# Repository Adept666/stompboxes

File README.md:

# -ТТКРЧПДЛ- / Тут короче педали

Здесь хранятся схемы и чертежи гитарных педалек *-ТТКРЧПДЛ-* (штаб-квартира: Омск, Сибирь). Купить педальки и задать вопросы можно через группу [ВКонтакте](https://vk.com/stompboxes), [Telegram-канал](https://t.me/stompboxes) или [Авито](https://www.avito.ru/brands/177f59860cf553edd7d790a341953521). Заценить звук можно на [YouTube-канале](https://youtube.com/channel/UCtStMn9qLL_V5MzlzgSMkUA). Поддержать можно с помощью [Boosty](https://boosty.to/stompboxes). Проект катастрофически убыточен и за семь лет съел тонну моих личных средств.

## Big Muff [REV3]

[Gerber](/PCBS-PCAS/ТКП-3.30.A/output/big_muff_r3a_gerber.zip)

### Bass

[Schematic](/PCBS-PCAS/ТКП-3.30.A/ТКП-1.30.A-2/output/ТКП-1.30.A-2-SCH.pdf)

[F_Fab](/PCBS-PCAS/ТКП-3.30.A/ТКП-1.30.A-2/output/ТКП-1.30.A-2-FAB-TOP.pdf)

[B_Fab](/PCBS-PCAS/ТКП-3.30.A/ТКП-1.30.A-2/output/ТКП-1.30.A-2-FAB-BOTTOM.pdf)

### Bass SM

[Schematic](/PCBS-PCAS/ТКП-3.30.A/ТКП-1.30.A-4/output/ТКП-1.30.A-4-SCH.pdf)

[F_Fab](/PCBS-PCAS/ТКП-3.30.A/ТКП-1.30.A-4/output/ТКП-1.30.A-4-FAB-TOP.pdf)

[B_Fab](/PCBS-PCAS/ТКП-3.30.A/ТКП-1.30.A-4/output/ТКП-1.30.A-4-FAB-BOTTOM.pdf)

### NYC

[Schematic](/PCBS-PCAS/ТКП-3.30.A/ТКП-1.30.A-1/output/ТКП-1.30.A-1-SCH.pdf)

[F_Fab](/PCBS-PCAS/ТКП-3.30.A/ТКП-1.30.A-1/output/ТКП-1.30.A-1-FAB-TOP.pdf)

[B_Fab](/PCBS-PCAS/ТКП-3.30.A/ТКП-1.30.A-1/output/ТКП-1.30.A-1-FAB-BOTTOM.pdf)

### NYC SM

[Schematic](/PCBS-PCAS/ТКП-3.30.A/ТКП-1.30.A-3/output/ТКП-1.30.A-3-SCH.pdf)

[F_Fab](/PCBS-PCAS/ТКП-3.30.A/ТКП-1.30.A-3/output/ТКП-1.30.A-3-FAB-TOP.pdf)

[B_Fab](/PCBS-PCAS/ТКП-3.30.A/ТКП-1.30.A-3/output/ТКП-1.30.A-3-FAB-BOTTOM.pdf)

## Big Muff [REV2]

[Gerber](/PCBS-PCAS/ТКП-3.13.A/output/big_muff_r2a_gerber.zip)

### Bass

[Schematic](/PCBS-PCAS/ТКП-3.13.A/ТКП-1.13.A-2/output/ТКП-1.13.A-2-SCH.pdf)

[F_Fab](/PCBS-PCAS/ТКП-3.13.A/ТКП-1.13.A-2/output/ТКП-1.13.A-2-FAB-TOP.pdf)

[B_Fab](/PCBS-PCAS/ТКП-3.13.A/ТКП-1.13.A-2/output/ТКП-1.13.A-2-FAB-BOTTOM.pdf)

### NYC

[Schematic](/PCBS-PCAS/ТКП-3.13.A/ТКП-1.13.A-1/output/ТКП-1.13.A-1-SCH.pdf)

[F_Fab](/PCBS-PCAS/ТКП-3.13.A/ТКП-1.13.A-1/output/ТКП-1.13.A-1-FAB-TOP.pdf)

[B_Fab](/PCBS-PCAS/ТКП-3.13.A/ТКП-1.13.A-1/output/ТКП-1.13.A-1-FAB-BOTTOM.pdf)

## Crumbwave Multiplexer [REV1]

[Schematic](/PCBS-PCAS/ТКП-3.32.A/ТКП-1.32.A-1/output/ТКП-1.32.A-1-SCH.pdf)

[F_Fab](/PCBS-PCAS/ТКП-3.32.A/ТКП-1.32.A-1/output/ТКП-1.32.A-1-FAB-TOP.pdf)

[B_Fab](/PCBS-PCAS/ТКП-3.32.A/ТКП-1.32.A-1/output/ТКП-1.32.A-1-FAB-BOTTOM.pdf)

[Gerber](/PCBS-PCAS/ТКП-3.32.A/output/crumbwave_multiplexer_r1a_gerber.zip)

## Deep Blue Delay [REV3]

### [REV3C]

[Gerber](/PCBS-PCAS/ТКП-3.17.C/output/deep_blue_delay_r3c_gerber.zip)

### [C]

[Schematic](/PCBS-PCAS/ТКП-3.17.C/ТКП-1.17.C-1/output/ТКП-1.17.C-1-SCH.pdf)

[F_Fab](/PCBS-PCAS/ТКП-3.17.C/ТКП-1.17.C-1/output/ТКП-1.17.C-1-FAB-TOP.pdf)

### [C] SM

[Schematic](/PCBS-PCAS/ТКП-3.17.C/ТКП-1.17.C-2/output/ТКП-1.17.C-2-SCH.pdf)

[F_Fab](/PCBS-PCAS/ТКП-3.17.C/ТКП-1.17.C-2/output/ТКП-1.17.C-2-FAB-TOP.pdf)

### [REV3B]

[Gerber](/PCBS-PCAS/ТКП-3.17.B/output/deep_blue_delay_r3b_gerber.zip)

### [B]

[Schematic](/PCBS-PCAS/ТКП-3.17.B/ТКП-1.17.B-1/output/ТКП-1.17.B-1-SCH.pdf)

[F_Fab](/PCBS-PCAS/ТКП-3.17.B/ТКП-1.17.B-1/output/ТКП-1.17.B-1-FAB-TOP.pdf)

[B_Fab](/PCBS-PCAS/ТКП-3.17.B/ТКП-1.17.B-1/output/ТКП-1.17.B-1-FAB-BOTTOM.pdf)

### [B] SM

[Schematic](/PCBS-PCAS/ТКП-3.17.B/ТКП-1.17.B-2/output/ТКП-1.17.B-2-SCH.pdf)

[F_Fab](/PCBS-PCAS/ТКП-3.17.B/ТКП-1.17.B-2/output/ТКП-1.17.B-2-FAB-TOP.pdf)

[B_Fab](/PCBS-PCAS/ТКП-3.17.B/ТКП-1.17.B-2/output/ТКП-1.17.B-2-FAB-BOTTOM.pdf)

## Distortion + [REV2]

[Schematic](/PCBS-PCAS/ТКП-3.11.A/ТКП-1.11.A-1/output/ТКП-1.11.A-1-SCH.pdf)

[F_Fab](/PCBS-PCAS/ТКП-3.11.A/ТКП-1.11.A-1/output/ТКП-1.11.A-1-FAB-TOP.pdf)

[Gerber](/PCBS-PCAS/ТКП-3.11.A/output/distortion_+_r2a_gerber.zip)

## Edamamer [REV1]

[Schematic](/PCBS-PCAS/ТКП-3.28.A/ТКП-1.28.A-1/output/ТКП-1.28.A-1-SCH.pdf)

[F_Fab](/PCBS-PCAS/ТКП-3.28.A/ТКП-1.28.A-1/output/ТКП-1.28.A-1-FAB-TOP.pdf)

[B_Fab](/PCBS-PCAS/ТКП-3.28.A/ТКП-1.28.A-1/output/ТКП-1.28.A-1-FAB-BOTTOM.pdf)

[Gerber](/PCBS-PCAS/ТКП-3.28.A/output/edamamer_r1a_gerber.zip)

## Fishtaur [REV1]

### [REV1A]

[Gerber](/PCBS-PCAS/ТКП-3.21.A/output/fishtaur_r1a_gerber.zip)

### [A]

[Schematic](/PCBS-PCAS/ТКП-3.21.A/ТКП-1.21.A-1/output/ТКП-1.21.A-1-SCH.pdf)

[F_Fab](/PCBS-PCAS/ТКП-3.21.A/ТКП-1.21.A-1/output/ТКП-1.21.A-1-FAB-TOP.pdf)

### [A] SM

[Schematic](/PCBS-PCAS/ТКП-3.21.A/ТКП-1.21.A-2/output/ТКП-1.21.A-2-SCH.pdf)

[F_Fab](/PCBS-PCAS/ТКП-3.21.A/ТКП-1.21.A-2/output/ТКП-1.21.A-2-FAB-TOP.pdf)

## Fuzz Factory [REV1]

### Main Board [REV1D] / Potentiometer Board [REV1C]

[Schematic](/PCBS-PCAS/ТКП-3.14.D-ТКП-3.15.C/ТКП-1.14.D-1-ТКП-1.15.C-1/output/ТКП-1.14.D-1-ТКП-1.15.C-1-SCH.pdf)

[F_Fab](/PCBS-PCAS/ТКП-3.14.D-ТКП-3.15.C/ТКП-1.14.D-1-ТКП-1.15.C-1/output/ТКП-1.14.D-1-ТКП-1.15.C-1-FAB-TOP.pdf)

[Gerber (Main Board)](/PCBS-PCAS/ТКП-3.14.D-ТКП-3.15.C/output/fuzz_factory_main_board_r1d_gerber.zip)

[Gerber (Potentiometer Board)](/PCBS-PCAS/ТКП-3.14.D-ТКП-3.15.C/output/fuzz_factory_potentiometer_board_r1c_gerber.zip)

### Main Board [REV1C] / Potentiometer Board [REV1B]

[Schematic](/PCBS-PCAS/ТКП-3.14.C-ТКП-3.15.B/ТКП-1.14.C-1-ТКП-1.15.B-1/output/ТКП-1.14.C-1-ТКП-1.15.B-1-SCH.pdf)

[F_Fab](/PCBS-PCAS/ТКП-3.14.C-ТКП-3.15.B/ТКП-1.14.C-1-ТКП-1.15.B-1/output/ТКП-1.14.C-1-ТКП-1.15.B-1-FAB-TOP.pdf)

[Gerber (Main Board)](/PCBS-PCAS/ТКП-3.14.C-ТКП-3.15.B/output/fuzz_factory_main_board_r1c_gerber.zip)

[Gerber (Potentiometer Board)](/PCBS-PCAS/ТКП-3.14.B-ТКП-3.15.B/output/fuzz_factory_potentiometer_board_r1b_gerber.zip)

### Main Board [REV1B] / Potentiometer Board [REV1B]

[Schematic](/PCBS-PCAS/ТКП-3.14.B-ТКП-3.15.B/ТКП-1.14.B-1-ТКП-1.15.B-1/output/ТКП-1.14.B-1-ТКП-1.15.B-1-SCH.pdf)

[F_Fab](/PCBS-PCAS/ТКП-3.14.B-ТКП-3.15.B/ТКП-1.14.B-1-ТКП-1.15.B-1/output/ТКП-1.14.B-1-ТКП-1.15.B-1-FAB-TOP.pdf)

[B_Cuts](/PCBS-PCAS/ТКП-3.14.B-ТКП-3.15.B/ТКП-1.14.B-1-ТКП-1.15.B-1/output/ТКП-1.14.B-1-ТКП-1.15.B-1-CUTS-BOTTOM.pdf)

[B_Jumpers](/PCBS-PCAS/ТКП-3.14.B-ТКП-3.15.B/ТКП-1.14.B-1-ТКП-1.15.B-1/output/ТКП-1.14.B-1-ТКП-1.15.B-1-JUMPERS-BOTTOM.pdf)

[Gerber (Main Board)](/PCBS-PCAS/ТКП-3.14.B-ТКП-3.15.B/output/fuzz_factory_main_board_r1b_gerber.zip)

[Gerber (Potentiometer Board)](/PCBS-PCAS/ТКП-3.14.B-ТКП-3.15.B/output/fuzz_factory_potentiometer_board_r1b_gerber.zip)

## Good Grief Overdrive [REV1]

### [REV1B]

[Gerber](/PCBS-PCAS/ТКП-3.19.B/output/good_grief_overdrive_r1b_gerber.zip)

### [B]

[Schematic](/PCBS-PCAS/ТКП-3.19.B/ТКП-1.19.B-1/output/ТКП-1.19.B-1-SCH.pdf)

[F_Fab](/PCBS-PCAS/ТКП-3.19.B/ТКП-1.19.B-1/output/ТКП-1.19.B-1-FAB-TOP.pdf)

### [B] SM

[Schematic](/PCBS-PCAS/ТКП-3.19.B/ТКП-1.19.B-2/output/ТКП-1.19.B-2-SCH.pdf)

[F_Fab](/PCBS-PCAS/ТКП-3.19.B/ТКП-1.19.B-2/output/ТКП-1.19.B-2-FAB-TOP.pdf)

### [REV1A]

[Schematic](/PCBS-PCAS/ТКП-3.19.A/ТКП-1.19.A-1/output/ТКП-1.19.A-1-SCH.pdf)

[F_Fab](/PCBS-PCAS/ТКП-3.19.A/ТКП-1.19.A-1/output/ТКП-1.19.A-1-FAB-TOP.pdf)

[Gerber](/PCBS-PCAS/ТКП-3.19.A/output/good_grief_overdrive_r1a_gerber.zip)

## Great Depression Phaser [REV1]

[Schematic](/PCBS-PCAS/ТКП-3.40.A/ТКП-1.38.A-1/output/ТКП-1.38.A-1-SCH.pdf)

[F_Fab](/PCBS-PCAS/ТКП-3.40.A/ТКП-1.38.A-1/output/ТКП-1.38.A-1-FAB-TOP.pdf)

[B_Fab](/PCBS-PCAS/ТКП-3.40.A/ТКП-1.38.A-1/output/ТКП-1.38.A-1-FAB-BOTTOM.pdf)

[Gerber](/PCBS-PCAS/ТКП-3.40.A/output/phaser_a_r1a_gerber.zip)

## Little Angel Chorus [REV1]

[Schematic](/PCBS-PCAS/ТКП-3.12.A/ТКП-1.12.A-1/output/ТКП-1.12.A-1-SCH.pdf)

[F_Fab](/PCBS-PCAS/ТКП-3.12.A/ТКП-1.12.A-1/output/ТКП-1.12.A-1-FAB-TOP.pdf)

[B_Fab](/PCBS-PCAS/ТКП-3.12.A/ТКП-1.12.A-1/output/ТКП-1.12.A-1-FAB-BOTTOM.pdf)

[Gerber](/PCBS-PCAS/ТКП-3.12.A/output/little_angel_chorus_r1a_gerber.zip)

## Salty Phaser [REV1]

[Schematic](/PCBS-PCAS/ТКП-3.23.A/ТКП-1.23.A-1/output/ТКП-1.23.A-1-SCH.pdf)

[F_Fab](/PCBS-PCAS/ТКП-3.23.A/ТКП-1.23.A-1/output/ТКП-1.23.A-1-FAB-TOP.pdf)

[B_Fab](/PCBS-PCAS/ТКП-3.23.A/ТКП-1.23.A-1/output/ТКП-1.23.A-1-FAB-BOTTOM.pdf)

[F_Cuts](/PCBS-PCAS/ТКП-3.23.A/ТКП-1.23.A-1/output/ТКП-1.23.A-1-CUTS-TOP.pdf)

[B_Cuts](/PCBS-PCAS/ТКП-3.23.A/ТКП-1.23.A-1/output/ТКП-1.23.A-1-CUTS-BOTTOM.pdf)

[F_Jumpers](/PCBS-PCAS/ТКП-3.23.A/ТКП-1.23.A-1/output/ТКП-1.23.A-1-JUMPERS-TOP.pdf)

[B_Jumpers](/PCBS-PCAS/ТКП-3.23.A/ТКП-1.23.A-1/output/ТКП-1.23.A-1-JUMPERS-BOTTOM.pdf)

[Gerber](/PCBS-PCAS/ТКП-3.23.A/output/salty_phaser_r1a_gerber.zip)

## Копка Земли [REV1]

### [REV1B]

[Gerber](/PCBS-PCAS/ТКП-3.24.B/output/копка_земли_r1b_gerber.zip)

### [B] Down-Tuned

[Schematic](/PCBS-PCAS/ТКП-3.24.B/ТКП-1.24.B-1/output/ТКП-1.24.B-1-SCH.pdf)

[F_Fab](/PCBS-PCAS/ТКП-3.24.B/ТКП-1.24.B-1/output/ТКП-1.24.B-1-FAB-TOP.pdf)

### [B] Down-Tuned SM

[Schematic](/PCBS-PCAS/ТКП-3.24.B/ТКП-1.24.B-3/output/ТКП-1.24.B-3-SCH.pdf)

[F_Fab](/PCBS-PCAS/ТКП-3.24.B/ТКП-1.24.B-3/output/ТКП-1.24.B-3-FAB-TOP.pdf)

### [B] Standard-Tuned

[Schematic](/PCBS-PCAS/ТКП-3.24.B/ТКП-1.24.B-2/output/ТКП-1.24.B-2-SCH.pdf)

[F_Fab](/PCBS-PCAS/ТКП-3.24.B/ТКП-1.24.B-2/output/ТКП-1.24.B-2-FAB-TOP.pdf)

### [B] Standard-Tuned SM

[Schematic](/PCBS-PCAS/ТКП-3.24.B/ТКП-1.24.B-4/output/ТКП-1.24.B-4-SCH.pdf)

[F_Fab](/PCBS-PCAS/ТКП-3.24.B/ТКП-1.24.B-4/output/ТКП-1.24.B-4-FAB-TOP.pdf)

### [REV1A]

[Gerber](/PCBS-PCAS/ТКП-3.24.A/output/копка_земли_r1a_gerber.zip)

### [A] Down-Tuned

[Schematic](/PCBS-PCAS/ТКП-3.24.A/ТКП-1.24.A-1/output/ТКП-1.24.A-1-SCH.pdf)

[F_Fab](/PCBS-PCAS/ТКП-3.24.A/ТКП-1.24.A-1/output/ТКП-1.24.A-1-FAB-TOP.pdf)

### [A] Standard-Tuned

[Schematic](/PCBS-PCAS/ТКП-3.24.A/ТКП-1.24.A-2/output/ТКП-1.24.A-2-SCH.pdf)

[F_Fab](/PCBS-PCAS/ТКП-3.24.A/ТКП-1.24.A-2/output/ТКП-1.24.A-2-FAB-TOP.pdf)

## Крыса [REV1]

[Schematic](/PCBS-PCAS/ТКП-3.44.A/ТКП-1.40.A-1/output/ТКП-1.40.A-1-SCH.pdf)

[F_Fab](/PCBS-PCAS/ТКП-3.44.A/ТКП-1.40.A-1/output/ТКП-1.40.A-1-FAB-TOP.pdf)

[Gerber](/PCBS-PCAS/ТКП-3.44.A/output/clipper_a_r1a_gerber.zip)

## Тремоло Саши Огородникова [REV1]

### [REV1B]

[Schematic](/PCBS-PCAS/ТКП-3.25.B/ТКП-1.25.B-1/output/ТКП-1.25.B-1-SCH.pdf)

[F_Fab](/PCBS-PCAS/ТКП-3.25.B/ТКП-1.25.B-1/output/ТКП-1.25.B-1-FAB-TOP.pdf)

[B_Fab](/PCBS-PCAS/ТКП-3.25.B/ТКП-1.25.B-1/output/ТКП-1.25.B-1-FAB-BOTTOM.pdf)

[Gerber](/PCBS-PCAS/ТКП-3.25.B/output/тремоло_саши_огородникова_r1b_gerber.zip)

### [REV1A]

[Schematic](/PCBS-PCAS/ТКП-3.25.A/ТКП-1.25.A-1/output/ТКП-1.25.A-1-SCH.pdf)

[F_Fab](/PCBS-PCAS/ТКП-3.25.A/ТКП-1.25.A-1/output/ТКП-1.25.A-1-FAB-TOP.pdf)

[B_Fab](/PCBS-PCAS/ТКП-3.25.A/ТКП-1.25.A-1/output/ТКП-1.25.A-1-FAB-BOTTOM.pdf)

[F_Cuts](/PCBS-PCAS/ТКП-3.25.A/ТКП-1.25.A-1/output/ТКП-1.25.A-1-CUTS-TOP.pdf)

[B_Cuts](/PCBS-PCAS/ТКП-3.25.A/ТКП-1.25.A-1/output/ТКП-1.25.A-1-CUTS-BOTTOM.pdf)

[B_Jumpers](/PCBS-PCAS/ТКП-3.25.A/ТКП-1.25.A-1/output/ТКП-1.25.A-1-JUMPERS-BOTTOM.pdf)

[Gerber](/PCBS-PCAS/ТКП-3.25.A/output/тремоло_саши_огородникова_r1a_gerber.zip)

## Требования

Работа с исходными файлами осуществляется в программе [KiCad](https://kicad.org).

Для просмотра и редактирования принципиальных схем необходимо подключить следующие библиотеки символов:
* [KCL](https://github.com/Adept666/KCL)
* [SBKCL](/SBKCL)

Для работы с чертежами печатных узлов подключение библиотек не требуется, так как все использованные футпринты вшиты в файлы *.kicad_pcb. При необходимости футпринты могут быть найдены в библиотеках [KCL](https://github.com/Adept666/KCL) и [SBKCL](/SBKCL).

## Авторы

Основной разработчик: *Igor Ivanov* (*Игорь Иванов*).  
Связь: adept.666.1993@gmail.com • [Telegram](https://t.me/adept666_2) • [ВКонтакте](https://vk.com/igor_ivanov_93) • [Google Scholar](https://scholar.google.com/citations?user=dhN1LfkAAAAJ).

Репозиторий также содержит сторонние открытые изображения и шрифты, использованные при создании макетов рисунков, наносимых на корпуса педалей. Информация об авторах и лицензиях представлена в сопроводительных текстовых файлах, размещённых в соответствующих директориях.

## Лицензии

Настоящий репозиторий использует раздельное лицензирование:

* Основная часть файлов распространяется на условиях *GNU General Public License v3.0 or later*, если не указано иное.

* Проекты печатных плат [Clipper A](/PCBS-PCAS/ТКП-3.44.A) и [OCD](/PCBS-PCAS/ТКП-3.45.A) распространяются на условиях *CERN Open Hardware Licence Version 2 - Strongly Reciprocal*.

* Сторонние [изображения](/graphics/source_images) и [шрифты](/graphics/source_fonts) распространяются на условиях иных лицензий, указанных в соответствующих файлах.

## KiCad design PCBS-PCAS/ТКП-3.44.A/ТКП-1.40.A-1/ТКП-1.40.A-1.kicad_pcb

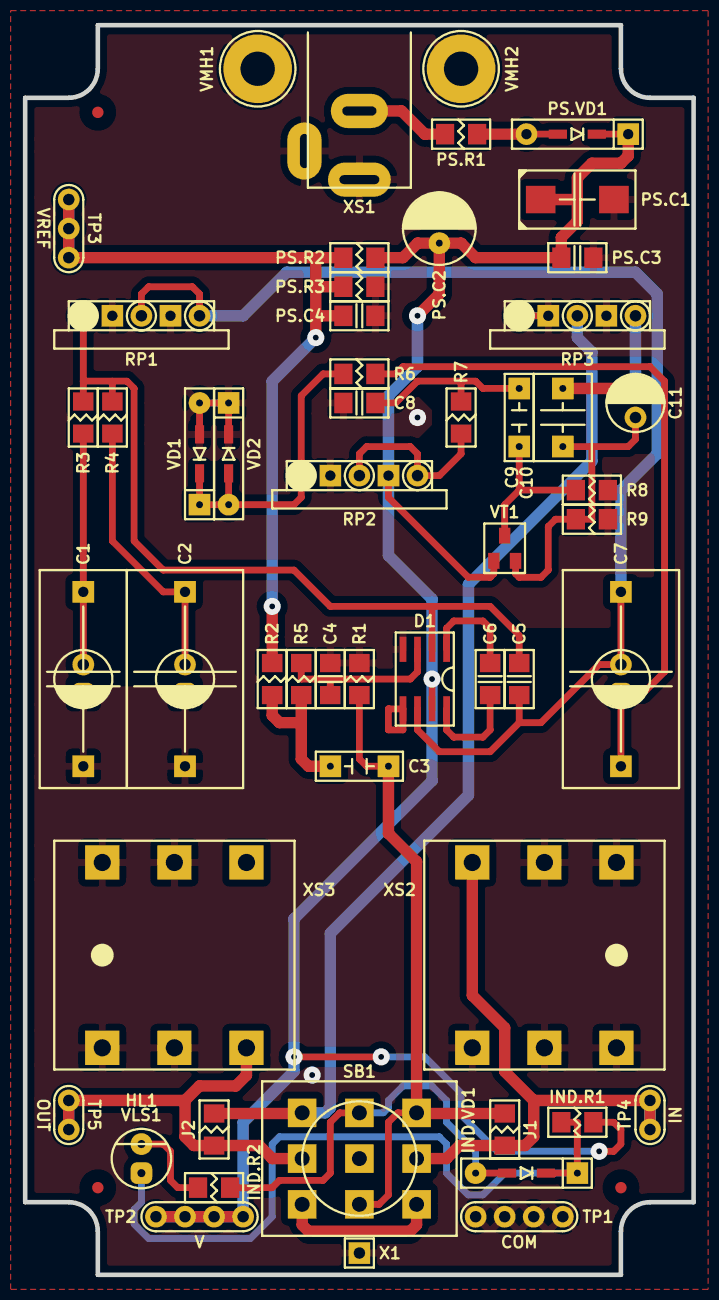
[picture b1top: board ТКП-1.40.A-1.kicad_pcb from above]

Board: 2 copper layers, 58.4 x 109.2 mm, 57 parts (0 on the bottom side), 28 nets.

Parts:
C1: 225; C-RECT-L18.0-W07.0-P15.24-d0.8-OR-CP-RADIAL-D05.0-P02.0-CLS
C2, C7: 475; C-RECT-L18.0-W09.0-P15.24-d0.8-OR-CP-RADIAL-D05.0-P02.0-CLS
C3, C9: 223; C-RECT-L07.3-W02.5-P05.08-d0.5
C4: 102; C-SM-1206
C5: 101; C-SM-1206
C6: X; C-SM-1206
C8: 332; C-SM-1206
C10: X; C-RECT-L07.3-W04.5-P05.08-d0.5
C11: 105; CP-RADIAL-D05.0-P02.0-CLS
D1: 07; P-SO-08
HL1: FYL-5013UWC; LED-ROUND-05.0-UNI-SH-SPACER
IND.R1: 182; R-SM-1206
IND.R2: 682; R-SM-1206
IND.VD1: 5235; P-SOD-123-OR-DO-35-V2
J1, J2: X; R-SM-1206
PS.C1: X; CP-CTSMD-D
PS.C2: 107; CP-RADIAL-D06.3-P02.5-d0.5-CLS
PS.C3: 104; C-SM-1206
PS.C4: 105; C-SM-1206
PS.R1: 470; R-SM-1206
PS.R2, PS.R3: 104; R-SM-1206
PS.VD1: 0540; P-SOD-123-OR-DO-41
R1, R2, R8: 105; R-SM-1206
R3: 470; R-SM-1206
R4: 561; R-SM-1206
R5, R6: 102; R-SM-1206
R7: 152; R-SM-1206
R9: 103; R-SM-1206
RP1, RP2, RP3: A100K; RPB-18-1x17-1.6
SB1: PBS-24-302SP; SW-PBS-24-302SP-2.5
TP1: COM; TP-4-1.0-1.9
TP2: V; TP-4-1.0-1.9
TP3: VREF; TP-3-1.0-1.9
TP4: IN; TP-2-1.0-1.9
TP5: OUT; TP-2-1.0-1.9
VD1, VD2: 4148; P-SOD-123-OR-DO-35-V2
VFM1, VFM2, VFM3: 1.0; VFM-1.0-3.0-SL
VLS1: BR-12.7; VLS-BR-P
VMH1, VMH2: X; VMH-STA-DA5
VT1: 5457; P-SOT-23-D-S-G
X1: X; CON-PAD-S-1.0-1.9
XS1: DC-005; CON-DC-005-9V-OVAL
XS2, XS3: PJ-644C; CON-PJ-644C-IN-OR-OUT

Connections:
/CIR-IN: C3.1, J1.2, R1.2, SB1.NC2, SB1.NO3
/CIR-OUT: J2.1, RP3.2, SB1.NO1
/IN: J1.1, SB1.COM3, TP4.1, XS2.T
/LED: IND.R2.1, IND.VD1.A, SB1.NO2
/OUT: J2.2, SB1.COM1, TP5.1, XS3.T
COM: C1.-, C2.-, C4.2, C8.2, D1.4, PS.C1.-, PS.C2.-, PS.C3.2, PS.C4.2, PS.R3.1, R1.1, R8.1, R9.1, RP1.NC1, RP1.NC2, RP2.NC1, RP3.1, RP3.NC1, RP3.NC2, SB1.COM2, TP1.1, VD1.A, VD2.C, VMH1.0, VMH2.0, X1.1, XS1.C, XS1.SN, XS2.R, XS2.RN, XS2.S, XS2.SN, XS2.TN, XS3.R, XS3.RN, XS3.S, XS3.SN
unnamed: C1.+, R3.1
unnamed: C2.+, R4.1
unnamed: C3.2, R2.2, R5.1
unnamed: C4.1, D1.3, R5.2
unnamed: C5.1, D1.2, R3.2, R4.2, RP1.1
unnamed: C5.2, C7.+, D1.6, RP1.2, RP1.3
unnamed: C6.1, D1.1
unnamed: C6.2, D1.8
unnamed: C7.-, R6.1
unnamed: C8.1, C9.1, R7.2
unnamed: C9.2, R8.2, VT1.G
unnamed: C10.1, C11.+, R9.2, VT1.S
unnamed: C10.2, C11.-, RP3.3
unnamed: HL1.A, IND.R1.2, IND.VD1.C
unnamed: HL1.C, IND.R2.2
unnamed: PS.R1.1, XS1.S
unnamed: PS.R1.2, PS.VD1.A
unnamed: R6.2, RP2.1, VD1.C, VD2.A
unnamed: R7.1, RP2.2, RP2.3
unnamed: SB1.NC1, SB1.NC3
V: D1.7, IND.R1.1, PS.C1.+, PS.C2.+, PS.C3.1, PS.R2.2, PS.VD1.C, RP2.NC2, TP2.1, VT1.D
VREF: PS.C4.1, PS.R2.1, PS.R3.2, R2.1, TP3.1

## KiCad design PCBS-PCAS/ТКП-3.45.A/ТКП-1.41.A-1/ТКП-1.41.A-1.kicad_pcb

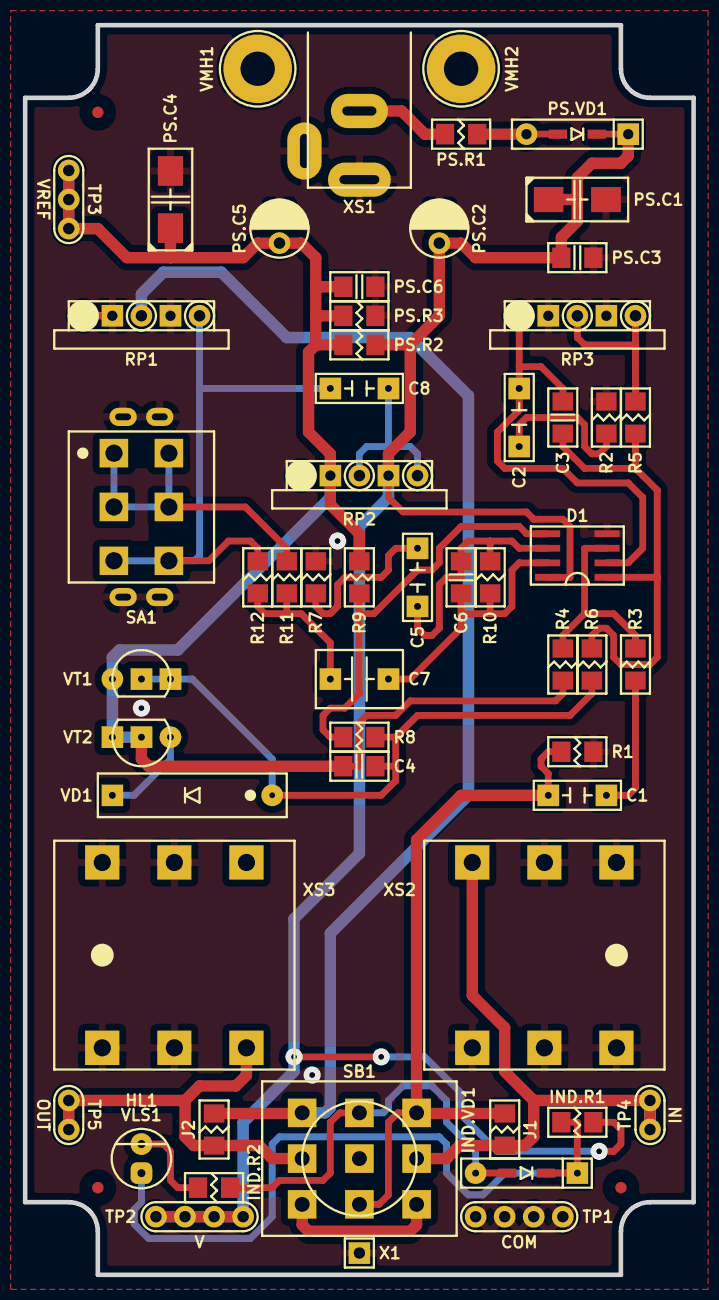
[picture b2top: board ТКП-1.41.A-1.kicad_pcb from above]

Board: 2 copper layers, 58.4 x 109.2 mm, 60 parts (0 on the bottom side), 29 nets.

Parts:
C1: 223; C-RECT-L07.3-W02.5-P05.08-d0.5
C2, C5, C8: 104; C-RECT-L07.3-W02.5-P05.08-d0.5
C3, C6: 221; C-SM-1206
C4: 102; C-SM-1206
C7: 105; C-RECT-L07.3-W04.5-P05.08-d0.5
D1: 082; P-SO-08
HL1: FYL-5013UWC; LED-ROUND-05.0-UNI-SH-SPACER
IND.R1: 182; R-SM-1206
IND.R2: 682; R-SM-1206
IND.VD1: 5235; P-SOD-123-OR-DO-35-V2
J1, J2: X; R-SM-1206
PS.C1: 106 35V; CP-CTSMD-C
PS.C2: 106 35V; CP-RADIAL-D05.0-P02.0-CLS
PS.C3, PS.C6: 104; C-SM-1206
PS.C4: 106 20V; CP-CTSMD-C
PS.C5: 106 25V; CP-RADIAL-D05.0-P02.0-CLS
PS.R1: 330; R-SM-1206
PS.R2, PS.R3: 103; R-SM-1206
PS.VD1: 0540; P-SOD-123-OR-DO-41
R1: 105; R-SM-1206
R2: 222; R-SM-1206
R3, R6, R8: 103; R-SM-1206
R4: 474; R-SM-1206
R5: 183; R-SM-1206
R7: 393; R-SM-1206
R9: 224; R-SM-1206
R10: 154; R-SM-1206
R11: 223; R-SM-1206
R12: 333; R-SM-1206
RP1: B100K; RPB-18-1x17-1.6
RP2: A25K; RPB-18-1x17-1.6
RP3: A500K; RPB-18-1x17-1.6
SA1: MTS-202-A2T; SW-MTS-202-A2T-2.5
SB1: PBS-24-302SP; SW-PBS-24-302SP-2.5
TP1: COM; TP-4-1.0-1.9
TP2: V; TP-4-1.0-1.9
TP3: VREF; TP-3-1.0-1.9
TP4: IN; TP-2-1.0-1.9
TP5: OUT; TP-2-1.0-1.9
VD1: Д9Б; P-Д-9
VFM1, VFM2, VFM3: 1.0; VFM-1.0-3.0-SL
VLS1: BR-12.7; VLS-BR-P
VMH1, VMH2: X; VMH-STA-DA5
VT1, VT2: 7000; P-TO-92-S-G-D
X1: COM; CON-PAD-S-1.0-1.9
XS1: DC-005; CON-DC-005-9V-OVAL
XS2, XS3: PJ-644C; CON-PJ-644C-IN-OR-OUT

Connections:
/CIR-IN: C1.1, J1.2, R1.2, SB1.NC2, SB1.NO3
/CIR-OUT: J2.1, RP1.2, SB1.NO1
/IN: J1.1, SB1.COM3, TP4.1, XS2.T
/LED: IND.R2.1, IND.VD1.A, SB1.NO2
/OUT: J2.2, SB1.COM1, TP5.1, XS3.T
COM: D1.4, PS.C1.-, PS.C2.-, PS.C3.2, PS.C4.-, PS.C5.-, PS.C6.2, PS.R3.1, R1.1, R2.1, R7.1, RP1.1, RP1.NC1, RP1.NC2, RP2.1, RP3.NC1, RP3.NC2, SA1.0, SB1.COM2, TP1.1, VMH1.0, VMH2.0, X1.1, XS1.C, XS1.SN, XS2.R, XS2.RN, XS2.S, XS2.SN, XS2.TN, XS3.R, XS3.RN, XS3.S, XS3.SN
unnamed: C1.2, R3.1
unnamed: C2.1, R2.2
unnamed: C2.2, C3.1, D1.2, RP3.1
unnamed: C3.2, D1.1, R5.1, R6.1
unnamed: C4.1, R6.2, R8.1, VD1.A, VT1.D, VT1.G
unnamed: C5.1, R7.2
unnamed: C5.2, C6.1, D1.6, R10.1
unnamed: C6.2, C7.1, D1.7, R10.2
unnamed: C7.2, R11.1, R12.1
unnamed: C8.1, R12.2, RP1.3, SA1.NO1, SA1.NO2
unnamed: C8.2, RP2.2, RP2.3
unnamed: D1.3, R3.2, R4.2
unnamed: D1.5, R8.2, R9.2
unnamed: HL1.A, IND.R1.2, IND.VD1.C
unnamed: HL1.C, IND.R2.2
unnamed: PS.R1.1, XS1.S
unnamed: PS.R1.2, PS.VD1.A
unnamed: R5.2, RP3.2, RP3.3
unnamed: R11.2, SA1.COM1, SA1.COM2, SA1.NC1, SA1.NC2
unnamed: SB1.NC1, SB1.NC3
unnamed: VD1.C, VT2.S
V: D1.8, IND.R1.1, PS.C1.+, PS.C2.+, PS.C3.1, PS.R2.2, PS.VD1.C, RP2.NC2, TP2.1
VREF: C4.2, PS.C4.+, PS.C5.+, PS.C6.1, PS.R2.1, PS.R3.2, R4.1, R9.1, RP2.NC1, TP3.1, VT1.S, VT2.D, VT2.G

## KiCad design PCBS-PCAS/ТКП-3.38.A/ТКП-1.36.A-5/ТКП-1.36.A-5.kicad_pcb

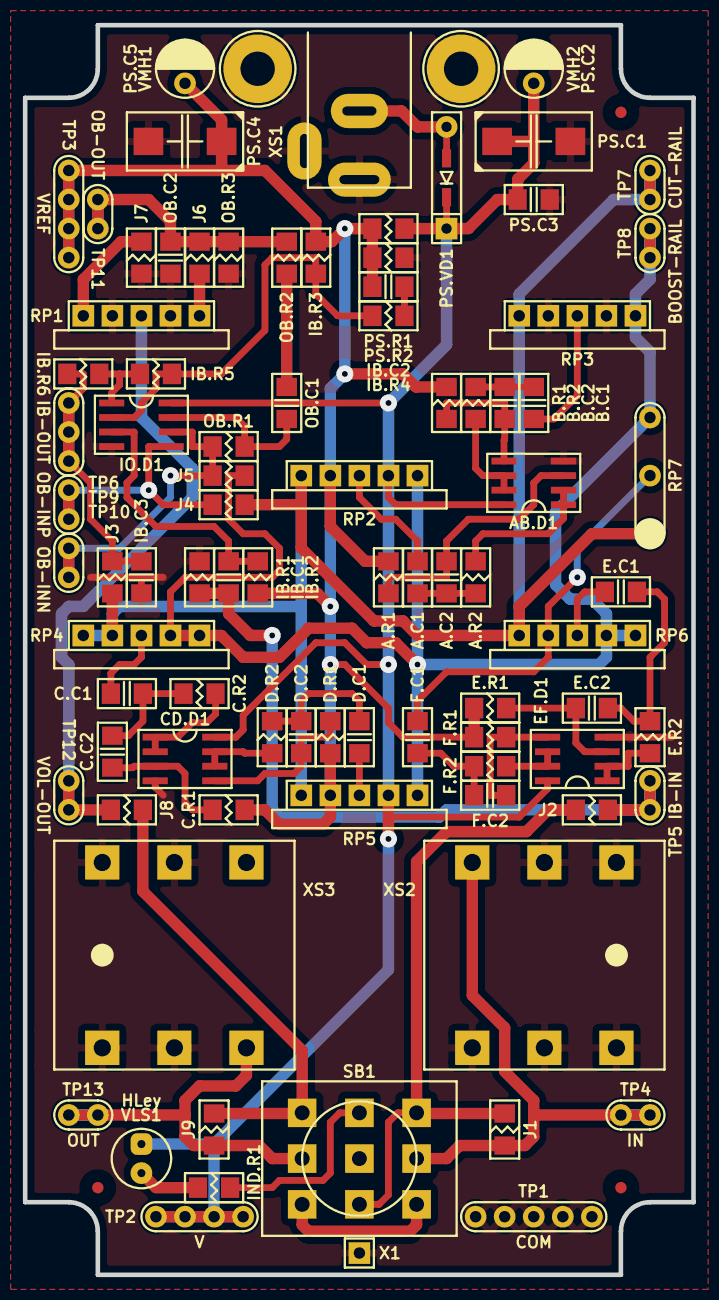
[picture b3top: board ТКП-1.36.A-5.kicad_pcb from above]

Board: 2 copper layers, 58.4 x 109.2 mm, 94 parts (0 on the bottom side), 51 nets.

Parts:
A.C1: 225; C-SM-1206
A.C2: 473; C-SM-1206
A.R1: 124; R-SM-1206
A.R2: 471; R-SM-1206
AB.D1: 4558; P-SO-08
B.C1: 105; C-SM-1206
B.C2: 333; C-SM-1206
B.R1: 104; R-SM-1206
B.R2: 471; R-SM-1206
C.C1: 154; C-SM-1206
C.C2: 682; C-SM-1206
C.R1: 104; R-SM-1206
C.R2: 102; R-SM-1206
CD.D1: 4558; P-SO-08
D.C1: 683; C-SM-1206
D.C2: 332; C-SM-1206
D.R1: 104; R-SM-1206
D.R2: 102; R-SM-1206
E.C1: 223; C-SM-1206
E.C2: 681; C-SM-1206
E.R1: 104; R-SM-1206
E.R2: 102; R-SM-1206
EF.D1: 4558; P-SO-08
F.C1, F.C2: X; C-SM-1206
F.R1, F.R2: X; R-SM-1206
HLeу: FYL-3014UWC; LED-ROUND-05.0-UNI-SH-SPACER-PNL-5.3
IB.C1, IB.C2: 103; C-SM-1206
IB.C3: 151; C-SM-1206
IB.R1: 225; R-SM-1206
IB.R2: 474; R-SM-1206
IB.R3, IB.R5, IB.R6: 103; R-SM-1206
IB.R4: 102; R-SM-1206
IND.R1: 433; R-SM-1206
IO.D1: 4558; P-SO-08
J1, J9: X; R-SM-1206
J2, J3, J4, J5, J6, J7, J8: 0; R-SM-1206
OB.C1: 105; C-SM-1206
OB.C2: 103; C-SM-1206
OB.R1, OB.R2, OB.R3: 103; R-SM-1206
PS.C1: 107; CP-CTSMD-D
PS.C2: 107; CP-RADIAL-D05.0-P02.0-CLS
PS.C3: 104; C-SM-1206
PS.C4: 476; CP-CTSMD-D
PS.C5: 476; CP-RADIAL-D05.0-P02.0-CLS
PS.R1, PS.R2: 473; R-SM-1206
PS.VD1: 0520; P-SOD-123-OR-DO-41
RP1, RP2, RP3, RP4, RP5, RP6: B50K; RPB-18-1x17-1.6-PNL-7.2
RP7: X; RP-EXTERNAL
SB1: PBS-24-302SP; SW-PBS-24-302SP-2.5-PNL-12.0
TP1: COM; TP-5-1.0-1.9
TP2: V; TP-4-1.0-1.9
TP3: VREF; TP-4-1.0-1.9
TP4: IN; TP-2-1.0-1.9
TP5: IB-IN; TP-2-1.0-1.9
TP6: IB-OUT; TP-3-1.0-1.9
TP7: CUT-RAIL; TP-2-1.0-1.9
TP8: BOOST-RAIL; TP-2-1.0-1.9
TP9: OB-INP; TP-2-1.0-1.9
TP10: OB-INN; TP-2-1.0-1.9
TP11: OB-OUT; TP-2-1.0-1.9
TP12: VOL-OUT; TP-2-1.0-1.9
TP13: OUT; TP-2-1.0-1.9
VE1: ТКП-6.3.1.A1.B1.A.1-1; ТКП-6.3.1.A1.B1.A
VE2: ТКП-6.3.3.A2.B1.3-1.B1.D1; ТКП-6.3.3.A2
VFM1, VFM2, VFM3: 1.0; VFM-1.0-3.0-SL
VLS1: 2xBR-7.7; VLS-BR
VMH1, VMH2: DI5M3x20; VMH-STA-DA5-PNL-3.0
X1: X; CON-PAD-S-1.0-1.9
XS1: DC-005; CON-DC-005-9V-OVAL
XS2, XS3: PJ-644C; CON-PJ-644C-IN-OR-OUT

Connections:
/BOOST-RAIL: J5.1, RP2.3, RP3.3, RP4.3, RP4.NC2, RP5.3, RP6.3, RP6.NC2, RP7.3, TP8.1
/CIR-IN: J1.2, J2.1, SB1.NC2, SB1.NO3
/CIR-OUT: J8.2, J9.1, SB1.NO1
/CUT-RAIL: J3.2, J4.1, RP2.1, RP3.1, RP4.1, RP4.NC1, RP5.1, RP6.1, RP7.1, TP7.1
/IB-IN: IB.C1.1, IB.R1.2, J2.2, TP5.1
/IB-OUT: IB.C3.1, IB.R6.2, J3.1, TP6.1
/IN: J1.1, SB1.COM3, TP4.1, XS2.T
/LED: IND.R1.1, SB1.NO2
/OB-INN: IO.D1.6, J5.2, OB.R1.1, TP10.1
/OB-INP: IO.D1.5, J4.2, TP9.1
/OB-OUT: J6.1, OB.C2.1, OB.R2.2, OB.R3.2, TP11.1
/OUT: J9.2, SB1.COM1, TP13.1, XS3.T
/VOL-COM: J7.1, RP1.1
/VOL-IN: J6.2, RP1.3
/VOL-OUT: J8.1, RP1.2, TP12.1
COM: AB.D1.4, CD.D1.4, EF.D1.4, IB.C3.2, IB.R1.1, IO.D1.4, J7.2, OB.C2.2, OB.R3.1, PS.C1.-, PS.C2.-, PS.C3.2, PS.C4.-, PS.C5.-, PS.R2.1, RP1.NC1, RP1.NC2, RP3.NC1, RP3.NC2, SB1.COM2, TP1.1, VMH1.0, VMH2.0, X1.1, XS1.C, XS1.SN, XS2.R, XS2.RN, XS2.S, XS2.SN, XS2.TN, XS3.R, XS3.RN, XS3.S, XS3.SN
unnamed: A.C1.1, RP2.2
unnamed: A.C1.2, A.C2.1, A.R2.1
unnamed: A.C2.2, A.R1.2, AB.D1.3
unnamed: A.R2.2, AB.D1.1, AB.D1.2
unnamed: AB.D1.5, B.C2.2, B.R1.2
unnamed: AB.D1.6, AB.D1.7, B.R2.2
unnamed: B.C1.1, RP3.2
unnamed: B.C1.2, B.C2.1, B.R2.1
unnamed: C.C1.1, RP4.2
unnamed: C.C1.2, C.C2.1, C.R2.1
unnamed: C.C2.2, C.R1.2, CD.D1.3
unnamed: C.R2.2, CD.D1.1, CD.D1.2
unnamed: CD.D1.5, D.C2.2, D.R1.2
unnamed: CD.D1.6, CD.D1.7, D.R2.2
unnamed: D.C1.1, RP5.2
unnamed: D.C1.2, D.C2.1, D.R2.1
unnamed: E.C1.1, RP6.2
unnamed: E.C1.2, E.C2.1, E.R2.1
unnamed: E.C2.2, E.R1.2, EF.D1.3
unnamed: E.R2.2, EF.D1.1, EF.D1.2
unnamed: EF.D1.5, F.C2.2, F.R1.2
unnamed: EF.D1.6, EF.D1.7, F.R2.2
unnamed: F.C1.1, RP6.NC1, RP7.2
unnamed: F.C1.2, F.C2.1, F.R2.1
unnamed: HLeу.C, IND.R1.2
unnamed: IB.C1.2, IB.R2.2, IO.D1.3
unnamed: IB.C2.2, IB.R4.1
unnamed: IB.R3.2, IB.R4.2, IB.R5.1, IO.D1.2
unnamed: IB.R5.2, IB.R6.1, IO.D1.1
unnamed: IO.D1.7, OB.C1.1, OB.R1.2
unnamed: OB.C1.2, OB.R2.1
unnamed: PS.VD1.A, XS1.S
unnamed: SB1.NC1, SB1.NC3
V: AB.D1.8, CD.D1.8, EF.D1.8, HLeу.A, IO.D1.8, PS.C1.+, PS.C2.+, PS.C3.1, PS.R1.2, PS.VD1.C, RP2.NC2, RP5.NC2, TP2.1
VREF: A.R1.1, B.R1.1, C.R1.1, D.R1.1, E.R1.1, F.R1.1, IB.C2.1, IB.R2.1, IB.R3.1, PS.C4.+, PS.C5.+, PS.R1.1, PS.R2.2, RP2.NC1, RP5.NC1, TP3.1

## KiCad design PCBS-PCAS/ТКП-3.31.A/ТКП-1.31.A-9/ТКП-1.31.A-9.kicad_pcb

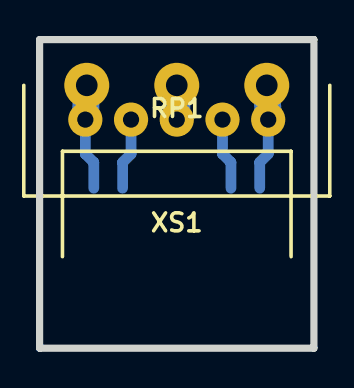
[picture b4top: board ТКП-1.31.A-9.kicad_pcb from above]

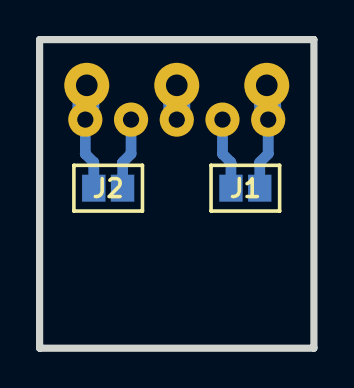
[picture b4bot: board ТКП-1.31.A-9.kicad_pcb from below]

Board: 2 copper layers, 15.2 x 17.1 mm, 4 parts (2 on the bottom side), 5 nets.

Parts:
J1: J1; J-SB-0805-2
J2: J2; J-SB-0805-2
RP1: B50K; RP-PDB181-K-20-P-CIRCULAR
XS1: PBS-05R; CON-PBS-05R-CIRCULAR

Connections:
unnamed: J1.1, RP1.3, XS1.1
unnamed: J1.2, XS1.2
unnamed: J2.1, XS1.4
unnamed: J2.2, RP1.1, XS1.5
unnamed: RP1.2, XS1.3

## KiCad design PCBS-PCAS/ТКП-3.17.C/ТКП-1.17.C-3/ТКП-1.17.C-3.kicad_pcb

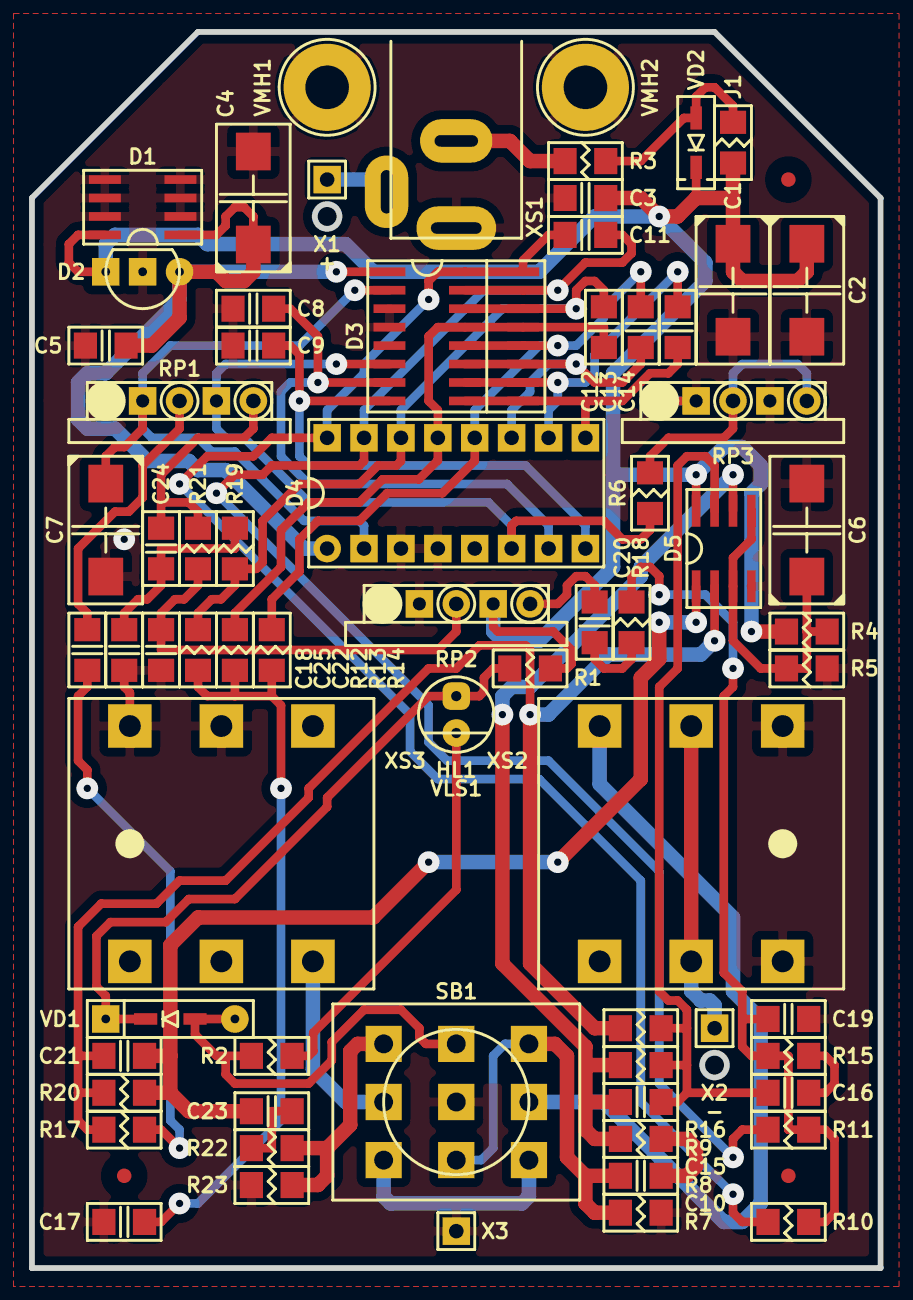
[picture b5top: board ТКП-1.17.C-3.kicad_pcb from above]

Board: 2 copper layers, 58.4 x 85.1 mm, 76 parts (0 on the bottom side), 45 nets.

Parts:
C1: 107; CP-CTSMD-D
C2: X; CP-CTSMD-D
C3, C5, C8, C9, C13, C14: 104; C-SM-1206
C4, C6, C7: 476; CP-CTSMD-D
C10, C20: 223; C-SM-1206
C11, C12: 222; C-SM-1206
C15: 470; C-SM-1206
C16, C18, C23, C24: 105; C-SM-1206
C17: 153; C-SM-1206
C19: 472; C-SM-1206
C21: 101; C-SM-1206
C22: 473; C-SM-1206
C25: 103; C-SM-1206
D1: 78L05; P-SO-08-OUT-GND-GND-NC-NC-GND-GND-IN
D2: 78L05; P-TO-92-OUT-GND-IN
D3: 8970; P-SO-16-OR-SO-16W
D4: 8970; P-DIP-16
D5: 5532; P-SO-08
GB1: X; B-PP3-HV
HL1: FYL-3014UWC; LED-ROUND-05.0-UNI-SH-SPACER-PNL-5.3
J1: X; R-SM-1206
R1, R3: 0; R-SM-1206
R2: 433; R-SM-1206
R4, R5, R10, R11, R13, R14, R15: 103; R-SM-1206
R6: 272; R-SM-1206
R7: 105; R-SM-1206
R8: 184; R-SM-1206
R9: 364; R-SM-1206
R12, R17: 203; R-SM-1206
R16: 223; R-SM-1206
R18: 512; R-SM-1206
R19, R22: 102; R-SM-1206
R20: 123; R-SM-1206
R21: 202; R-SM-1206
R23: 104; R-SM-1206
RP1, RP2, RP3: B50K; RPB-18-1x17-1.6-PNL-7.2
SB1: PBS-24-302SP; SW-PBS-24-302SP-2.5-PNL-12.0
VD1: X; P-SOD-123-OR-DO-35-V2
VD2: 0520; P-SOD-123
VE1: ТКП-6.3.1.A2.A1.A.1-1; ТКП-6.3.1.A2.A1.A
VE2: ТКП-6.3.3.A1.A1.3-1.A1.00; ТКП-6.3.3.A1
VFM1, VFM2, VFM3: 1.0; VFM-1.0-3.0-SL
VLS1: 2xBR-7.7; VLS-BR-P
VMH1, VMH2: DI5M3x20; VMH-STA-DA5-PNL-3.0
X1, X2, X3: X; CON-PAD-S-1.0-1.9
XS1: DC-005; CON-DC-005-9V-OVAL
XS2, XS3: PJ-644C; CON-PJ-644C-IN-OR-OUT

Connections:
/2: C7.+, D3.2, D4.2, RP1.NC1
/6: D3.6, D4.6, R6.2, RP1.NC2
/7: C8.2, D3.7, D4.7
/8: C9.2, D3.8, D4.8
/9: C14.2, D3.9, D4.9
/10: C14.1, D3.10, D4.10
/11: C13.2, D3.11, D4.11
/12: C13.1, D3.12, D4.12, R14.1
/13: C12.2, D3.13, D4.13, R13.1
/14: C12.1, D3.14, D4.14, R12.1, R19.1
/15: C11.2, D3.15, D4.15, R11.1
/16: C11.1, D3.16, D4.16, R10.1
/IN-CIR: C10.1, R7.2, SB1.NC2, SB1.NO3
/IN-CON: SB1.COM3, XS2.T
/LED: R2.1, SB1.NO2, VD1.A
/OUT-CIR: R22.2, R23.2, SB1.NO1
/OUT-CON: SB1.COM1, XS3.T
/PP3-NEG: X2.1, XS2.R, XS2.RN
/PP3-POS: X1.1, XS1.SN
COM: C1.-, C2.-, C3.2, C4.-, C5.2, C6.-, C7.-, C8.1, C9.1, C17.2, C19.2, C22.2, C25.2, D1.GND, D1.NC, D2.GND, D3.3, D3.4, D4.3, D4.4, D5.4, R5.1, R7.1, R23.1, RP1.1, RP2.1, RP2.NC1, RP3.1, RP3.NC1, RP3.NC2, SB1.COM2, VMH1.0, VMH2.0, X3.1, XS1.C, XS2.S, XS2.SN, XS2.TN, XS3.R, XS3.RN, XS3.S, XS3.SN
unnamed: C10.2, R8.1
unnamed: C15.1, D5.6, R8.2, R9.1
unnamed: C15.2, C16.1, D5.7, R9.2, R16.1
unnamed: C16.2, R15.2
unnamed: C17.1, R12.2, R13.2, R14.2
unnamed: C18.1, R17.1
unnamed: C18.2, RP1.2
unnamed: C19.1, R10.2, R11.2, R15.1, R18.2
unnamed: C20.1, R18.1
unnamed: C20.2, RP2.3
unnamed: C21.1, D5.2, R16.2, R17.2, R20.1
unnamed: C21.2, C23.1, D5.1, R20.2
unnamed: C22.1, R21.1, RP2.2
unnamed: C23.2, R22.1
unnamed: C24.1, R21.2, RP1.3
unnamed: C24.2, C25.1, R19.2
unnamed: HL1.A, R1.2, VD1.C
unnamed: HL1.C, R2.2
unnamed: J1.1, R3.2, VD2.A
unnamed: R3.1, XS1.S
unnamed: R6.1, RP3.2, RP3.3
unnamed: SB1.NC1, SB1.NC3
V: C1.+, C2.+, C3.1, D1.IN, D2.IN, D5.8, J1.2, R1.1, R4.2, RP2.NC2, VD2.C
VA: C4.+, C5.1, D1.OUT, D2.OUT, D3.1, D4.1
VREF: C6.+, D5.3, D5.5, R4.1, R5.2

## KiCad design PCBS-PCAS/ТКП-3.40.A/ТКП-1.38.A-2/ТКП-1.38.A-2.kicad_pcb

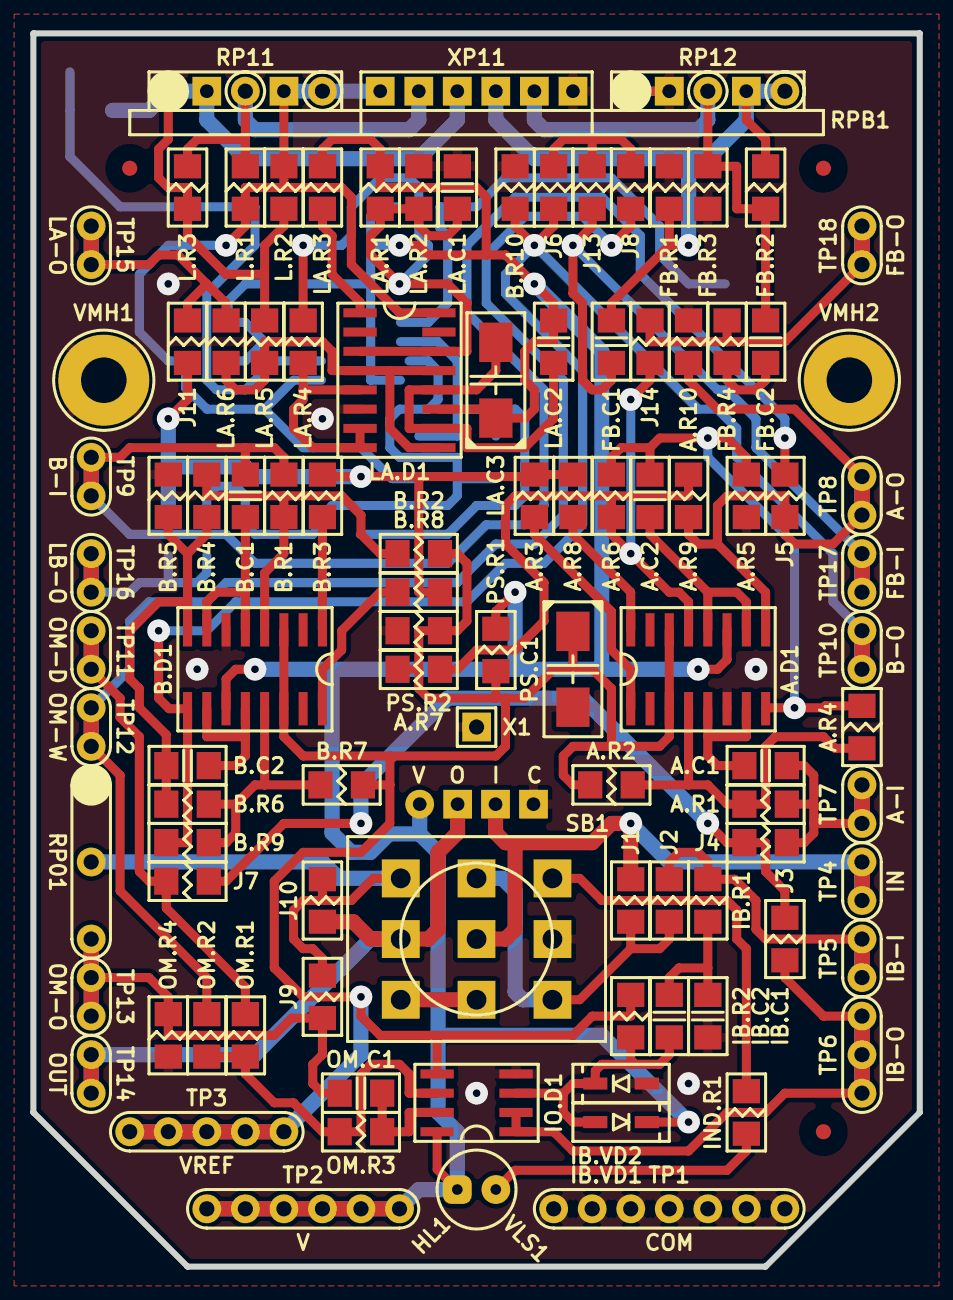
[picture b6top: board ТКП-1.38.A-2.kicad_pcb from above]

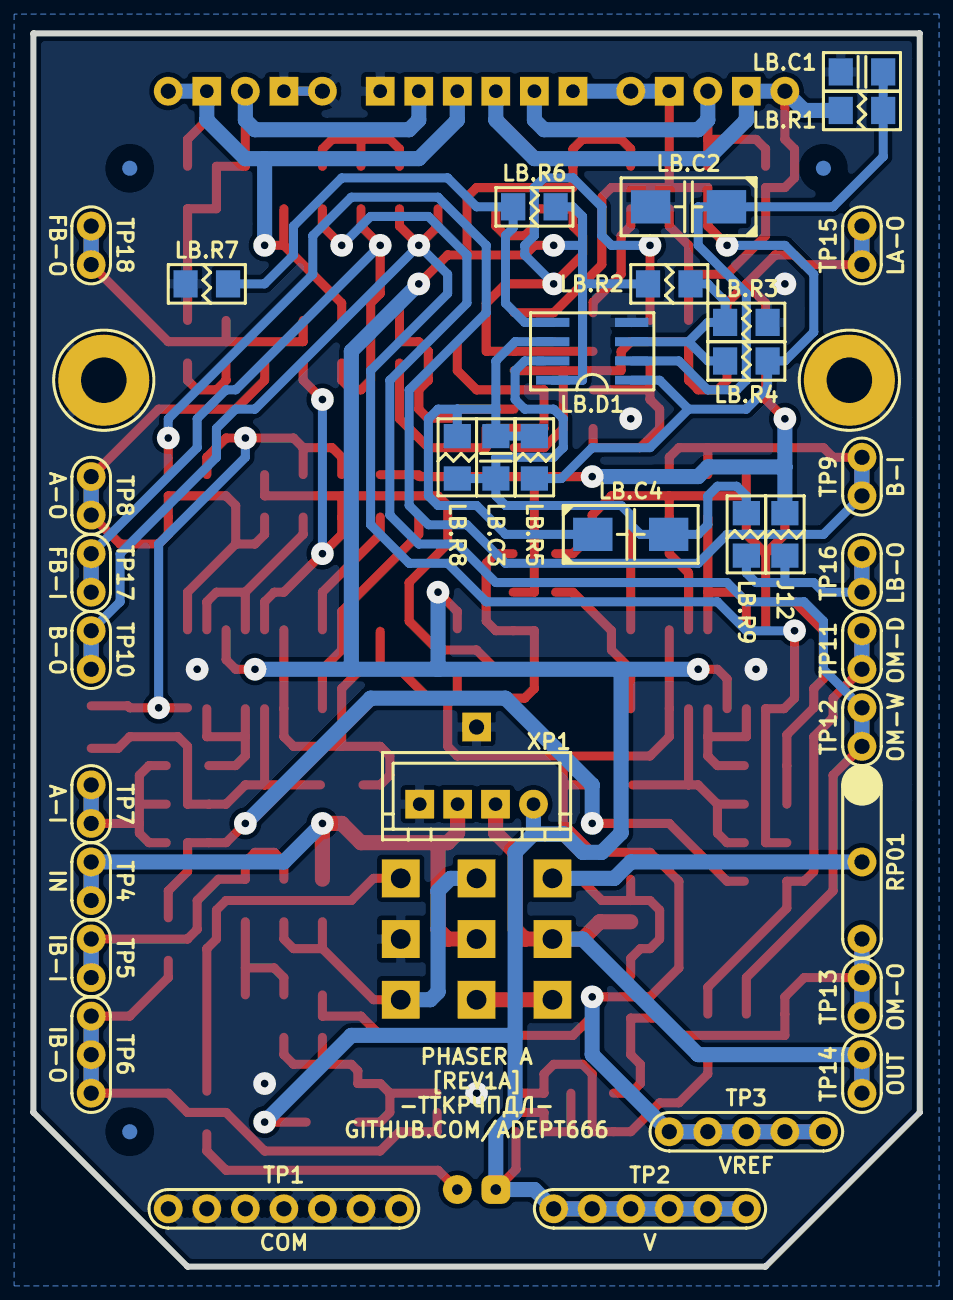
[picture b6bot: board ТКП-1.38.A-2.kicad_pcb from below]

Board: 2 copper layers, 58.4 x 81.3 mm, 122 parts (16 on the bottom side), 60 nets.

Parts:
A.C1, A.C2: 332; C-SM-1206
A.D1: 13700; P-SO-16
A.R1, A.R4, A.R6, A.R9: 273; R-SM-1206
A.R2, A.R7: 182; R-SM-1206
A.R3, A.R8: 0; R-SM-1206
A.R5, A.R10: 103; R-SM-1206
B.C1, B.C2: 332; C-SM-1206
B.D1: 13700; P-SO-16
B.R1, B.R4, B.R6, B.R9: 273; R-SM-1206
B.R2, B.R7: 182; R-SM-1206
B.R3, B.R8: 0; R-SM-1206
B.R5, B.R10: 103; R-SM-1206
FB.C1, FB.C2: 105; C-SM-1206
FB.R1, FB.R3: X; R-SM-1206
FB.R2, FB.R4: 273; R-SM-1206
HL1: FYL-5013UWC; LED-ROUND-05.0-UNI-SH-SPACER-PNL-6.6
IB.C1: 101; C-SM-1206
IB.C2: 103; C-SM-1206
IB.R1: 102; R-SM-1206
IB.R2: 474; R-SM-1206
IB.VD1, IB.VD2: 4148; P-SOD-123
IND.R1: 103; R-SM-1206
IO.D1: 4558; P-SO-08
J1, J10, J12: X; R-SM-1206
J2, J3, J4, J5, J6, J7, J8, J9, J11, J13, J14: 0; R-SM-1206
L.R1, L.R2: X; R-SM-1206
L.R3: 0; R-SM-1206
LA.C1: 473; C-SM-1206
LA.C2: 335; C-SM-1206
LA.C3: X; CP-CTSMD-C
LA.D1: 13700; P-SO-16
LA.R1, LA.R3: 274; R-SM-1206
LA.R2: 104; R-SM-1206
LA.R4, LA.R6: 103; R-SM-1206
LA.R5: 682; R-SM-1206
LB.C1, LB.C3: X; C-SM-1206
LB.C2, LB.C4: X; CP-CTSMD-C
LB.D1: X; P-SO-08
LB.R1, LB.R2, LB.R3, LB.R4, LB.R5, LB.R6, LB.R7, LB.R8, LB.R9: X; R-SM-1206
OM.C1: 105; C-SM-1206
OM.R1, OM.R2: 273; R-SM-1206
OM.R3: 153; R-SM-1206
OM.R4: 154; R-SM-1206
PS.C1: 106; CP-CTSMD-C
PS.R1, PS.R2: 103; R-SM-1206
RP01: X; RP-EXTERNAL
RPB1: B50K-B50K; RPB-1590N1-18-2x17-OR-2x1x17-1.6-PNL-7.2
SB1: PBS-24-302SP; SW-PBS-24-302SP-2.5-PNL-12.0
TP1: COM; TP-7-1.0-1.9
TP2: V; TP-6-1.0-1.9
TP3: VREF; TP-5-1.0-1.9
TP4: IN; TP-2-1.0-1.9
TP5: IB-I; TP-2-1.0-1.9
TP6: IB-O; TP-3-1.0-1.9
TP7: A-I; TP-2-1.0-1.9
TP8: A-O; TP-2-1.0-1.9
TP9: B-I; TP-2-1.0-1.9
TP10: B-O; TP-2-1.0-1.9
TP11: OM-D; TP-2-1.0-1.9
TP12: OM-W; TP-2-1.0-1.9
TP13: OM-O; TP-2-1.0-1.9
TP14: OUT; TP-2-1.0-1.9
TP15: LA-O; TP-2-1.0-1.9
TP16: LB-O; TP-2-1.0-1.9
TP17: FB-I; TP-2-1.0-1.9
TP18: FB-O; TP-2-1.0-1.9
VE1: ТКП-6.2.1.A1.A1.A.1-1; ТКП-6.2.1.A1.A1.A
VE2: ТКП-6.2.4.A1.B1.4-1.A2.B1; ТКП-6.2.4.A1
VFM1, VFM2, VFM3: 1.0; VFM-1.0-3.0-DL
VLS1: BR-9.52; VLS-BR
VMH1, VMH2: DI5M3x18; VMH-STA-DA5-PNL-3.0
X1: X; CON-PAD-S-1.0-1.9
XB1: 1590N1 Connector Board; XB-1590N1
XP1: B4B-XH-A; CON-XH-B4B-A

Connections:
/A-IN: A.C1.1, A.R1.1, J4.2, TP7.1
/A-OUT: A.D1.9, A.R9.2, A.R10.1, J5.1, TP8.1
/B-IN: B.C1.1, B.R1.1, J5.2, TP9.1
/B-OUT: B.D1.9, B.R9.2, B.R10.1, J6.1, TP10.1
/CIR-IN: J1.2, J2.1, SB1.NC3, SB1.NO2
/CIR-OUT: J9.2, J10.1, RP01.2, SB1.NO1
/DRY: J3.2, J4.1, J7.1
/FB: A.D1.13, A.R6.2, A.R7.1, A.R9.1, J14.2
/FB-IN: FB.C1.1, J13.2, TP17.1
/FB-OUT: FB.R4.2, J14.1, TP18.1
/IB-IN: IB.R1.1, J2.2, TP5.1
/IB-OUT: IO.D1.1, IO.D1.2, J3.1, TP6.1
/IN: J1.1, SB1.COM2, TP4.1, XP1.3
/LED: IND.R1.1, SB1.NO3
/LFO: A.R3.1, A.R8.1, B.R3.1, B.R8.1, J11.2, J12.2
/LFOA-OUT: J11.1, LA.R6.2, TP15.1
/LFOB-OUT: J12.1, LB.R9.2, TP16.1
/OM-INDRY: J7.2, OM.R1.2, TP11.1
/OM-INWET: J8.2, OM.R2.1, TP12.1
/OM-OUT: J9.1, OM.C1.2, OM.R4.2, RP01.3, TP13.1
/OUT: J10.2, SB1.COM1, TP14.1, XP1.2
/RP11-1: L.R2.2, L.R3.2, LA.R5.1, LB.R1.2, RPB1.11, RPB1.NC1
/RP11-2: L.R1.2, L.R3.1, RPB1.12
/RP11-3: L.R1.1, L.R2.1, LA.D1.16, LB.D1.1, LB.R4.2, LB.R5.1, RPB1.13, RPB1.NC2
/WET: J6.2, J8.1, J13.1
COM: A.D1.6, A.R5.2, A.R10.2, B.D1.6, B.R5.2, B.R10.2, FB.R1.1, FB.R3.1, IB.C1.2, IB.VD2.A, IO.D1.4, LA.C1.2, LA.D1.6, LA.R2.1, LB.C1.1, LB.C2.-, LB.D1.4, LB.R3.1, LB.R7.1, OM.R4.1, PS.C1.-, PS.R2.1, RP01.1, RPB1.21, RPB1.NC3, SB1.COM3, TP1.1, VMH1.0, VMH2.0, X1.1, XP1.4
unnamed: A.C1.2, A.D1.5, A.D1.7
unnamed: A.C2.1, A.D1.8, A.R4.2, A.R5.1, A.R6.1
unnamed: A.C2.2, A.D1.10, A.D1.12
unnamed: A.D1.1, A.R3.2
unnamed: A.D1.4, A.R1.2, A.R2.1, A.R4.1
unnamed: A.D1.16, A.R8.2
unnamed: B.C1.2, B.D1.5, B.D1.7
unnamed: B.C2.1, B.D1.8, B.R4.2, B.R5.1, B.R6.1
unnamed: B.C2.2, B.D1.10, B.D1.12
unnamed: B.D1.1, B.R3.2
unnamed: B.D1.4, B.R1.2, B.R2.1, B.R4.1
unnamed: B.D1.13, B.R6.2, B.R7.1, B.R9.1
unnamed: B.D1.16, B.R8.2
unnamed: FB.C1.2, FB.R1.2, FB.R2.2, RPB1.23, RPB1.NC4
unnamed: FB.C2.1, FB.R2.1, FB.R3.2, RPB1.22
unnamed: FB.C2.2, FB.R4.1
unnamed: HL1.C, IND.R1.2
unnamed: IB.C1.1, IB.C2.1, IB.R1.2
unnamed: IB.C2.2, IB.R2.2, IB.VD1.A, IB.VD2.C, IO.D1.3
unnamed: IO.D1.6, OM.R1.1, OM.R2.2, OM.R3.1
unnamed: IO.D1.7, OM.C1.1, OM.R3.2
unnamed: LA.C1.1, LA.D1.3, LA.D1.14, LA.R1.1, LA.R2.2, LA.R4.1
unnamed: LA.C2.2, LA.C3.-, LA.D1.10, LA.D1.12
unnamed: LA.D1.1, LA.R3.1
unnamed: LA.D1.5, LA.D1.7, LA.D1.8, LA.R4.2
unnamed: LA.D1.4, LA.D1.9, LA.D1.13, LA.R5.2, LA.R6.1
unnamed: LB.C1.2, LB.C2.+, LB.D1.2, LB.R1.1
unnamed: LB.C3.1, LB.C4.+, LB.D1.6, LB.R5.2, LB.R8.1
unnamed: LB.C3.2, LB.C4.-, LB.D1.7, LB.R8.2, LB.R9.1
unnamed: LB.D1.3, LB.R2.2, LB.R3.2, LB.R4.1
unnamed: LB.D1.5, LB.R6.1, LB.R7.2
unnamed: SB1.NC1, SB1.NC2
V: A.D1.11, B.D1.11, HL1.A, IB.VD1.C, IO.D1.8, LA.C2.1, LA.C3.+, LA.D1.11, LA.R1.2, LA.R3.2, LB.D1.8, LB.R2.1, LB.R6.2, PS.R1.2, TP2.1, XP1.1
VREF: A.D1.3, A.D1.14, A.R2.2, A.R7.2, B.D1.3, B.D1.14, B.R2.2, B.R7.2, IB.R2.1, IO.D1.5, PS.C1.+, PS.R1.1, PS.R2.2, TP3.1

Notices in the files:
PCBS-PCAS/ТКП-3.17.C/ТКП-1.17.C-3/ТКП-1.17.C-3.kicad_pcb:
This project is licensed under GNU General Public License v3.0 or later
PCBS-PCAS/ТКП-3.44.A/ТКП-1.40.A-1/ТКП-1.40.A-1.kicad_pcb:
This project is licensed under CERN-OHL-S-2.0
CERN-OHL-S-2.0
